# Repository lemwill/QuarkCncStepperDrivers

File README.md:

# QuarkCncStepperDrivers

Work in progress

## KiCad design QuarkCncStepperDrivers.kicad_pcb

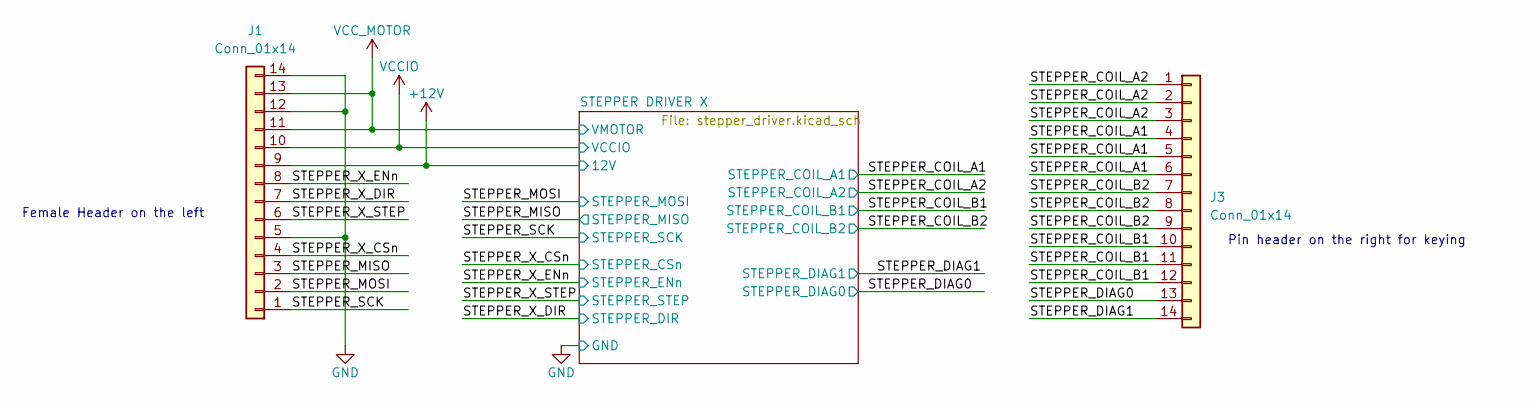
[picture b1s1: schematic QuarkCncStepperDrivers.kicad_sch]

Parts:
J1, J3: Conn_01x14; PinHeader_1x14_P2.54mm_Vertical; LCSC C2894937

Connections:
+3V3: J1.10; also elsewhere on the board
+12V: J1.9; also elsewhere on the board
/STEPPER_COIL_A1: J3.4, J3.5, J3.6; also elsewhere on the board
/STEPPER_COIL_A2: J3.1, J3.2, J3.3; also elsewhere on the board
/STEPPER_COIL_B1: J3.10, J3.11, J3.12; also elsewhere on the board
/STEPPER_COIL_B2: J3.7, J3.8, J3.9; also elsewhere on the board
/STEPPER_DIAG0: J3.13; also elsewhere on the board
/STEPPER_DIAG1: J3.14; also elsewhere on the board
/STEPPER_MISO: J1.3; also elsewhere on the board
/STEPPER_MOSI: J1.2; also elsewhere on the board
/STEPPER_SCK: J1.1; also elsewhere on the board
/STEPPER_X_CSn: J1.4; also elsewhere on the board
/STEPPER_X_DIR: J1.7; also elsewhere on the board
/STEPPER_X_ENn: J1.8; also elsewhere on the board
/STEPPER_X_STEP: J1.6; also elsewhere on the board
GND: J1.5, J1.12, J1.14; also elsewhere on the board
VCC: J1.11, J1.13; also elsewhere on the board

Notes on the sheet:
Female Header on the left
Pin header on the right for keying

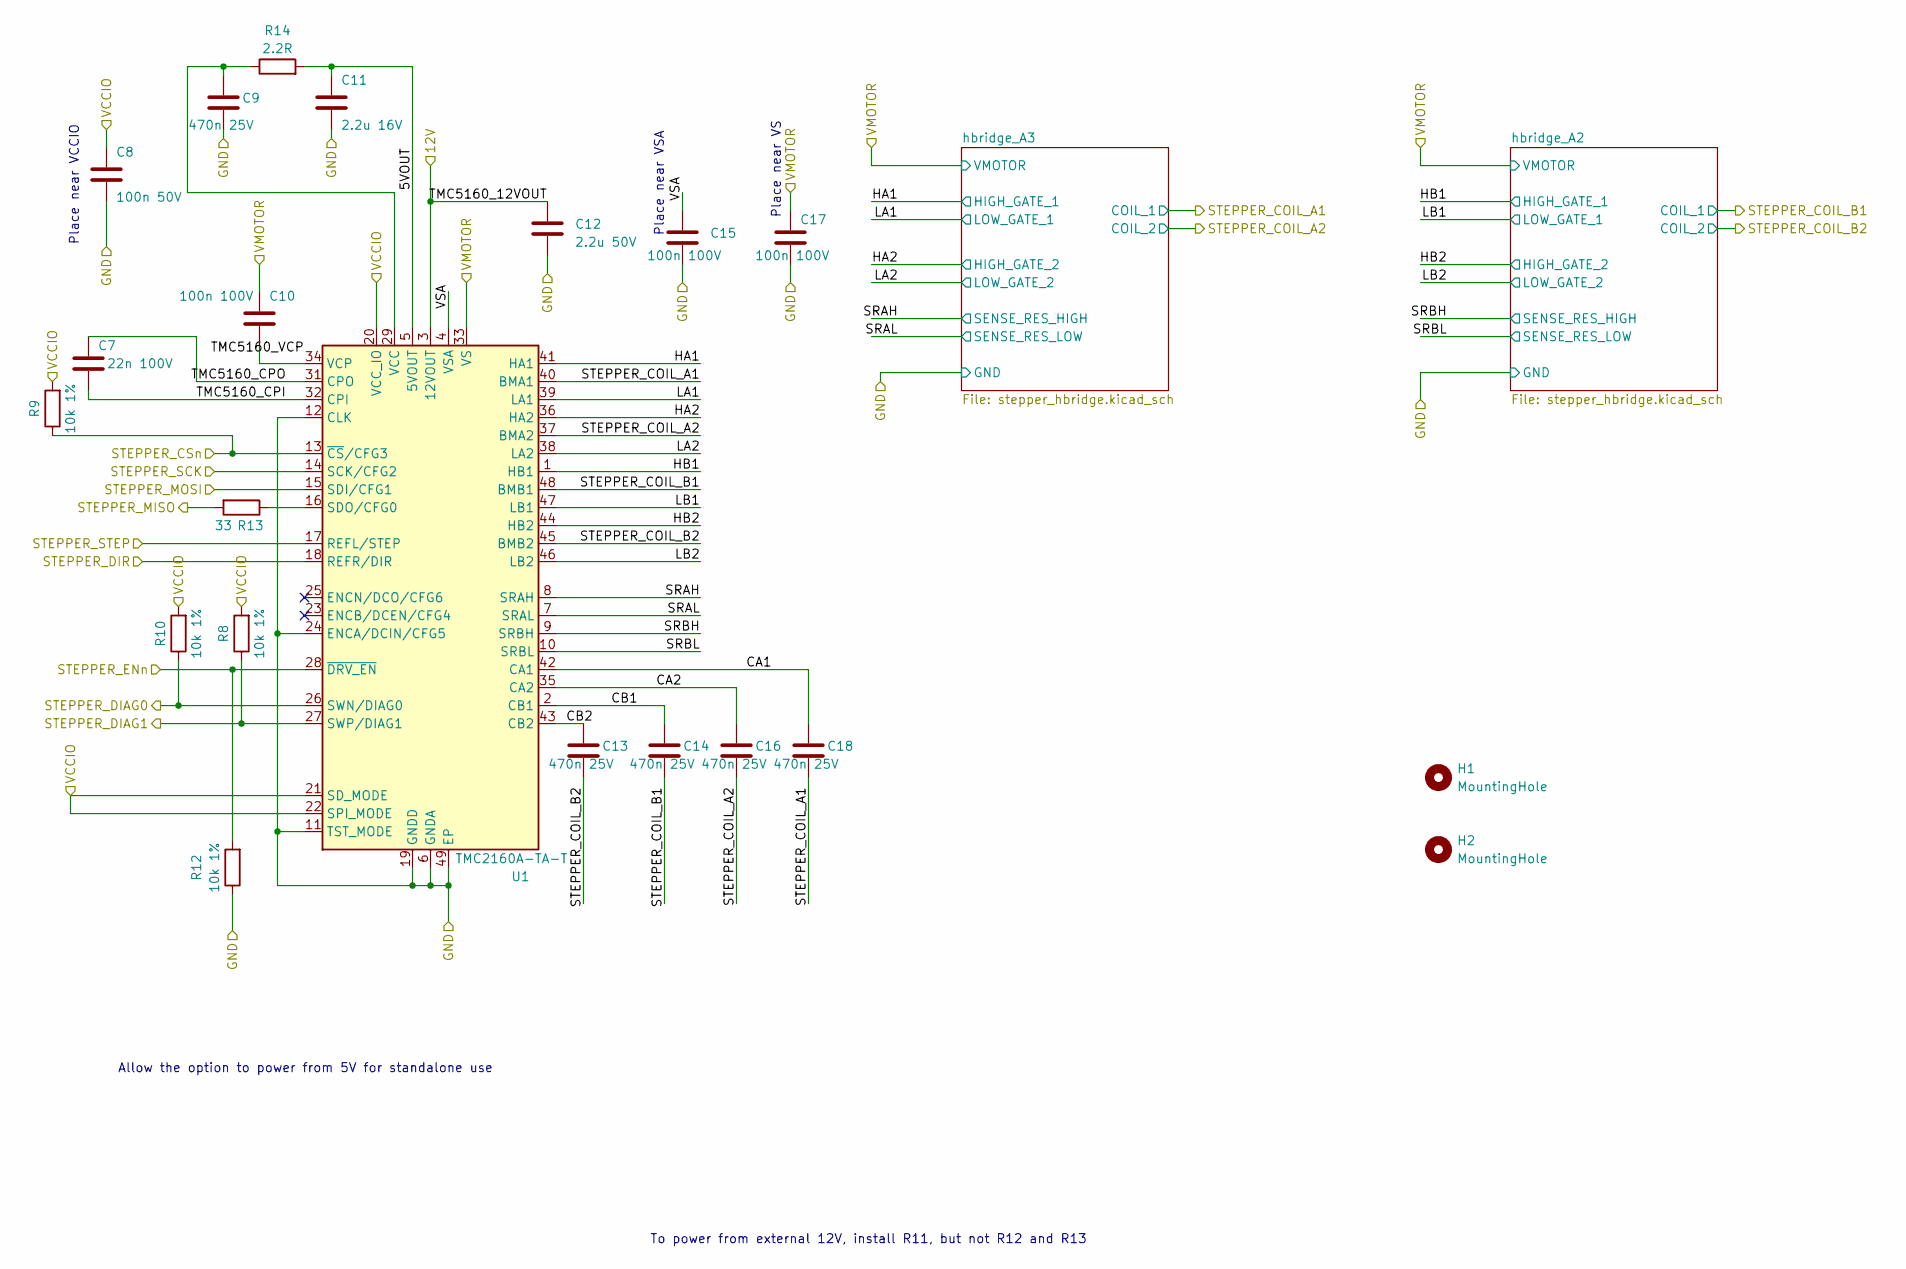
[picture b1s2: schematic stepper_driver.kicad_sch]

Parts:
C7: 22n 100V; C_0402_1005Metric; LCSC C1532
C8: 100n 50V; C_0402_1005Metric; LCSC C307331
C9, C13, C14, C16, C18: 470n 25V; C_0603_1608Metric; LCSC C1623
C10, C15, C17: 100n 100V; C_0805_2012Metric_Pad1.18x1.45mm_HandSolder; LCSC C28233
C11: 2.2u 16V; C_0603_1608Metric; LCSC C23630
C12: 2.2u 50V; C_0805_2012Metric; LCSC C49217
H1, H2: MountingHole; MountingHole_3.2mm_M3
R8, R9, R10, R12: 10k 1%; R_0402_1005Metric; LCSC C25744
R13: 33; R_0402_1005Metric; LCSC C25105
R14: 2.2R; R_0603_1608Metric; LCSC C22939
U1: TMC2160A-TA-T; TQFP-48-1EP_7x7mm_P0.5mm_EP5x5mm_ThermalVias; LCSC C465948

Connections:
+3V3: C8.1, R8.2, R9.2, R10.2, U1.20 (VCC_IO), U1.21 (SD_MODE), U1.22 (SPI_MODE); also elsewhere on the board
+12V: C12.1, U1.3 (12VOUT); also elsewhere on the board
/STEPPER DRIVER X/5VOUT: C11.1, R14.2, U1.5 (5VOUT)
/STEPPER DRIVER X/CA1: C18.1, U1.42 (CA1)
/STEPPER DRIVER X/CA2: C16.1, U1.35 (CA2)
/STEPPER DRIVER X/CB1: C14.1, U1.2 (CB1)
/STEPPER DRIVER X/CB2: C13.1, U1.43 (CB2)
/STEPPER DRIVER X/HA1: U1.41 (HA1); also elsewhere on the board
/STEPPER DRIVER X/HA2: U1.36 (HA2); also elsewhere on the board
/STEPPER DRIVER X/HB1: U1.1 (HB1); also elsewhere on the board
/STEPPER DRIVER X/HB2: U1.44 (HB2); also elsewhere on the board
/STEPPER DRIVER X/LA1: U1.39 (LA1); also elsewhere on the board
/STEPPER DRIVER X/LA2: U1.38 (LA2); also elsewhere on the board
/STEPPER DRIVER X/LB1: U1.47 (LB1); also elsewhere on the board
/STEPPER DRIVER X/LB2: U1.46 (LB2); also elsewhere on the board
/STEPPER DRIVER X/SRAH: U1.8 (SRAH); also elsewhere on the board
/STEPPER DRIVER X/SRAL: U1.7 (SRAL); also elsewhere on the board
/STEPPER DRIVER X/SRBH: U1.9 (SRBH); also elsewhere on the board
/STEPPER DRIVER X/SRBL: U1.10 (SRBL); also elsewhere on the board
/STEPPER DRIVER X/TMC5160_CPI: C7.2, U1.32 (CPI)
/STEPPER DRIVER X/TMC5160_CPO: C7.1, U1.31 (CPO)
/STEPPER DRIVER X/VSA: C15.1, U1.4 (VSA)
/STEPPER_COIL_A1: C18.2, U1.40 (BMA1); also elsewhere on the board
/STEPPER_COIL_A2: C16.2, U1.37 (BMA2); also elsewhere on the board
/STEPPER_COIL_B1: C14.2, U1.48 (BMB1); also elsewhere on the board
/STEPPER_COIL_B2: C13.2, U1.45 (BMB2); also elsewhere on the board
/STEPPER_DIAG0: R10.1, U1.26 (SWN/DIAG0); also elsewhere on the board
/STEPPER_DIAG1: R8.1, U1.27 (SWP/DIAG1); also elsewhere on the board
/STEPPER_MISO: R13.2; also elsewhere on the board
/STEPPER_MOSI: U1.15 (SDI/CFG1); also elsewhere on the board
/STEPPER_SCK: U1.14 (SCK/CFG2); also elsewhere on the board
/STEPPER_X_CSn: R9.1, U1.13 (~CS/CFG3); also elsewhere on the board
/STEPPER_X_DIR: U1.18 (REFR/DIR); also elsewhere on the board
/STEPPER_X_ENn: R12.2, U1.28 (~DRV_EN); also elsewhere on the board
/STEPPER_X_STEP: U1.17 (REFL/STEP); also elsewhere on the board
GND: C8.2, C9.2, C11.2, C12.2, C15.2, C17.2, R12.1, U1.6 (GNDA), U1.11 (TST_MODE), U1.12 (CLK), U1.19 (GNDD), U1.24 (ENCA/DCIN/CFG5), U1.30 (GNDD), U1.49 (EP); also elsewhere on the board
unnamed: R13.1, U1.16 (SDO/CFG0)
unnamed: C9.1, R14.1, U1.29 (VCC)
unnamed: C10.2, U1.34 (VCP)
VCC: C10.1, C17.1, U1.33 (VS); also elsewhere on the board

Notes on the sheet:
Place near VSA
Place near VS
Allow the option to power from 5V for standalone use
Place near VCCIO
To power from external 12V, install R11, but not R12 and R13

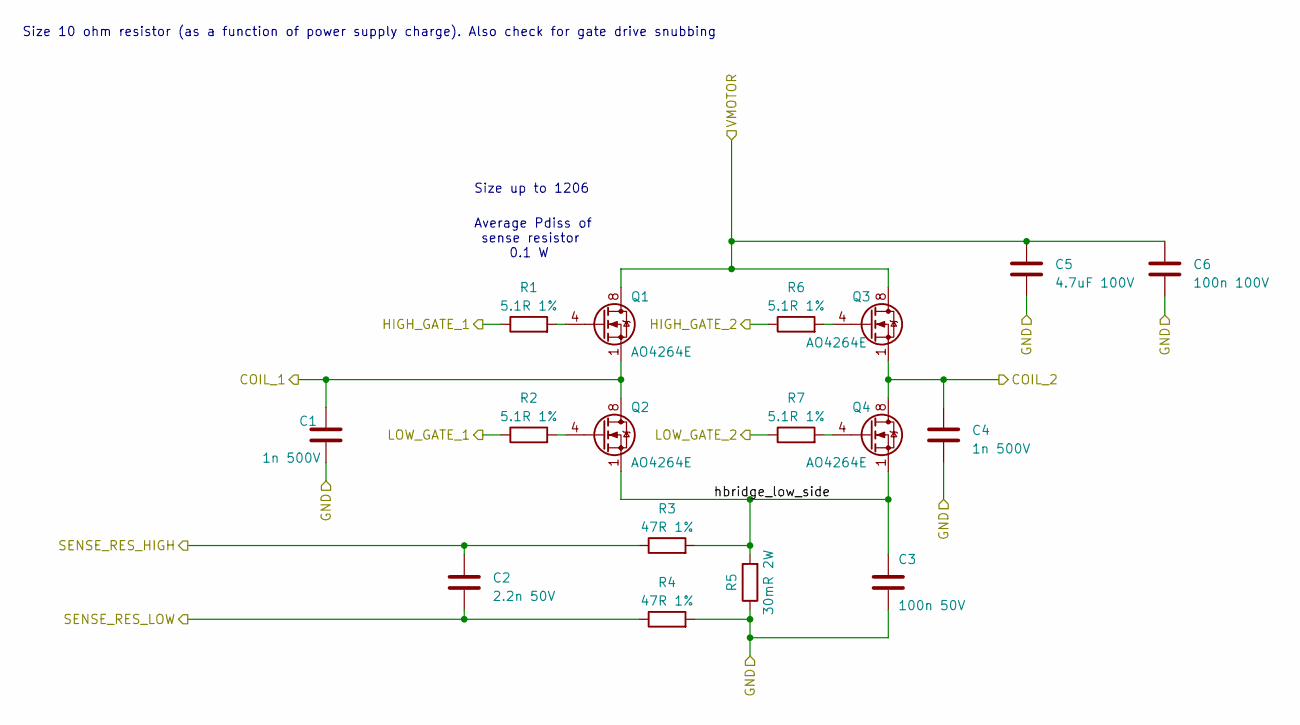
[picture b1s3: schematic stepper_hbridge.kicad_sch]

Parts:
C1, C4: 1n 500V; C_1206_3216Metric; LCSC C35216
C2: 2.2n 50V; C_0603_1608Metric; LCSC C1604
C3: 100n 50V; C_0402_1005Metric; LCSC C307331
C5: 4.7uF 100V; C_1210_3225Metric; LCSC C385986
C6: 100n 100V; C_0805_2012Metric_Pad1.18x1.45mm_HandSolder; LCSC C28233
Q1, Q2, Q3, Q4: AO4264E; SOIC-8_3.9x4.9mm_P1.27mm; LCSC C334232
R1, R2, R6, R7: 5.1R 1%; R_0805_2012Metric; LCSC C17724
R3, R4: 47R 1%; R_0402_1005Metric; LCSC C25118
R5: 30mR 2W; R_2512_6332Metric; LCSC C493478

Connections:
/STEPPER DRIVER X/HA1: R1.1; also elsewhere on the board
/STEPPER DRIVER X/HA2: R6.1; also elsewhere on the board
/STEPPER DRIVER X/LA1: R2.1; also elsewhere on the board
/STEPPER DRIVER X/LA2: R7.1; also elsewhere on the board
/STEPPER DRIVER X/SRAH: C2.1, R3.1; also elsewhere on the board
/STEPPER DRIVER X/SRAL: C2.2, R4.1; also elsewhere on the board
/STEPPER DRIVER X/hbridge_A3/hbridge_low_side: C3.1, Q2.1 (S), Q2.2 (S), Q2.3 (S), Q4.1 (S), Q4.2 (S), Q4.3 (S), R3.2, R5.2
/STEPPER_COIL_A1: C1.1, Q1.1 (S), Q1.2 (S), Q1.3 (S), Q2.5 (D), Q2.6 (D), Q2.7 (D), Q2.8 (D); also elsewhere on the board
/STEPPER_COIL_A2: C4.1, Q3.1 (S), Q3.2 (S), Q3.3 (S), Q4.5 (D), Q4.6 (D), Q4.7 (D), Q4.8 (D); also elsewhere on the board
GND: C1.2, C3.2, C4.2, C5.2, C6.2, R4.2, R5.1; also elsewhere on the board
unnamed: Q1.4 (G), R1.2
unnamed: Q2.4 (G), R2.2
unnamed: Q3.4 (G), R6.2
unnamed: Q4.4 (G), R7.2
VCC: C5.1, C6.1, Q1.5 (D), Q1.6 (D), Q1.7 (D), Q1.8 (D), Q3.5 (D), Q3.6 (D), Q3.7 (D), Q3.8 (D); also elsewhere on the board

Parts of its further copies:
C19, C22: 1n 500V; C_1206_3216Metric; LCSC C35216
C20: 2.2n 50V; C_0603_1608Metric; LCSC C1604
C21: 100n 50V; C_0402_1005Metric; LCSC C307331
C23: 4.7uF 100V; C_1210_3225Metric; LCSC C385986
C24: 100n 100V; C_0805_2012Metric_Pad1.18x1.45mm_HandSolder; LCSC C28233
Q5, Q6, Q7, Q8: AO4264E; SOIC-8_3.9x4.9mm_P1.27mm; LCSC C334232
R19, R20, R24, R25: 5.1R 1%; R_0805_2012Metric; LCSC C17724
R21, R22: 47R 1%; R_0402_1005Metric; LCSC C25118
R23: 30mR 2W; R_2512_6332Metric; LCSC C493478

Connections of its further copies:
/STEPPER DRIVER X/HB1: R19.1; also elsewhere on the board
/STEPPER DRIVER X/HB2: R24.1; also elsewhere on the board
/STEPPER DRIVER X/LB1: R20.1; also elsewhere on the board
/STEPPER DRIVER X/LB2: R25.1; also elsewhere on the board
/STEPPER DRIVER X/SRBH: C20.1, R21.1; also elsewhere on the board
/STEPPER DRIVER X/SRBL: C20.2, R22.1; also elsewhere on the board
/STEPPER DRIVER X/hbridge_A2/hbridge_low_side: C21.1, Q6.1 (S), Q6.2 (S), Q6.3 (S), Q8.1 (S), Q8.2 (S), Q8.3 (S), R21.2, R23.2
/STEPPER_COIL_B1: C19.1, Q5.1 (S), Q5.2 (S), Q5.3 (S), Q6.5 (D), Q6.6 (D), Q6.7 (D), Q6.8 (D); also elsewhere on the board
/STEPPER_COIL_B2: C22.1, Q7.1 (S), Q7.2 (S), Q7.3 (S), Q8.5 (D), Q8.6 (D), Q8.7 (D), Q8.8 (D); also elsewhere on the board
GND: C19.2, C21.2, C22.2, C23.2, C24.2, R22.2, R23.1; also elsewhere on the board
unnamed: Q5.4 (G), R19.2
unnamed: Q6.4 (G), R20.2
unnamed: Q7.4 (G), R24.2
unnamed: Q8.4 (G), R25.2
VCC: C23.1, C24.1, Q5.5 (D), Q5.6 (D), Q5.7 (D), Q5.8 (D), Q7.5 (D), Q7.6 (D), Q7.7 (D), Q7.8 (D); also elsewhere on the board

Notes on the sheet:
Size up to 1206
Size 10 ohm resistor (as a function of power supply charge). Also check for gate drive snubbing
Average Pdiss of sense resistor 0.1 W

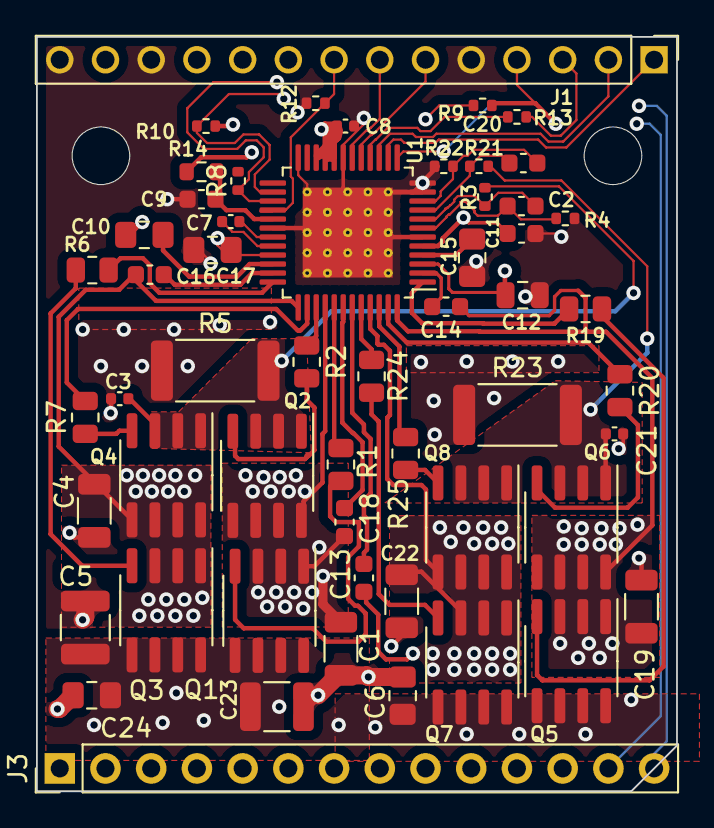
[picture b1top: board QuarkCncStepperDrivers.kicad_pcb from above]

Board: 4 copper layers, 35.6 x 41.9 mm, 57 parts (0 on the bottom side), 50 nets.

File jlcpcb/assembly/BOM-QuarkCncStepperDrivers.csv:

Comment,Designator,Footprint,LCSC
22n 100V,C7,C_0402_1005Metric,C1532
2.2n 50V,"C2,C20",C_0603_1608Metric,C1604
470n 25V,"C13,C14,C16,C18,C9",C_0603_1608Metric,C1623
0R,R15,R_0402_1005Metric,C17168
5.1R 1%,"R1,R19,R2,R20,R24,R25,R6,R7",R_0805_2012Metric,C17724
2.2R,R14,R_0603_1608Metric,C22939
2.2u 16V,C11,C_0603_1608Metric,C23630
33,R13,R_0402_1005Metric,C25105
47R 1%,"R21,R22,R3,R4",R_0402_1005Metric,C25118
10k 1%,"R10,R11,R12,R9",R_0402_1005Metric,C25744
100n 100V,"C10,C15,C17,C24,C6",C_0805_2012Metric_Pad1.18x1.45mm_HandSolder,C28233
Conn_01x14,"J1,J2",PinHeader_1x14_P2.54mm_Vertical,C2894937
100n 50V,"C21,C3,C8",C_0402_1005Metric,C307331
AO4264E,"Q1,Q2,Q3,Q4,Q5,Q6,Q7,Q8",SOIC-8_3.9x4.9mm_P1.27mm,C334232
1n 500V,"C1,C19,C22,C4",C_1206_3216Metric,C35216
4.7uF 100V,"C23,C5",C_1210_3225Metric,C385986
TMC2160A-TA-T,U1,TQFP-48-1EP_7x7mm_P0.5mm_EP5x5mm_ThermalVias,C465948
2.2u 50V,C12,C_0805_2012Metric,C49217
30mR 2W,"R23,R5",R_2512_6332Metric,C493478
MountingHole,H2,MountingHole_3.2mm_M3,
0R DNI,R18,R_0805_2012Metric,
0R DNI,R17,R_0402_1005Metric,
MountingHole,H1,MountingHole_3.2mm_M3,
0R DNI,R16,R_0402_1005Metric,

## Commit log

2022-05-31 Create LICENSE
2022-05-31 Added symbol library
2022-08-06 Removed caps from board. Will be placed on main board
2022-08-06 Added pdf
2022-08-23 Added assembly files
2022-09-16 triple connector
2022-09-21 Removed 0Ohms. Keyed design
2023-05-10 Updated pinout
